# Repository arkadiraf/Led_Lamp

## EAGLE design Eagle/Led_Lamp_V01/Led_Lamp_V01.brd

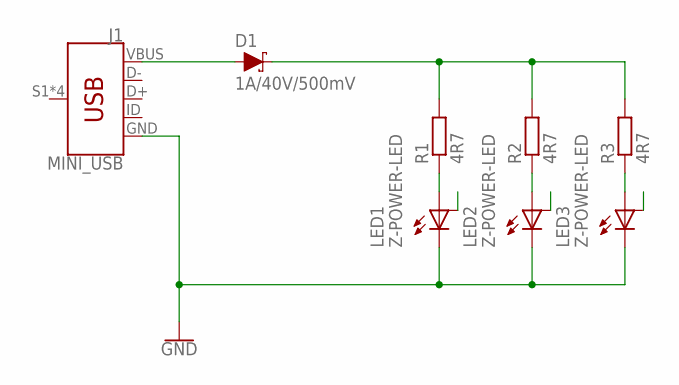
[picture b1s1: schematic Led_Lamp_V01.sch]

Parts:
D1: 1A/40V/500mV; SMA-DIODE
J1: MINI_USB; USB-MINIB
LED1, LED2, LED3: Z-POWER-LED; Z-POWER-LED-PCB-TYPE
R1, R2, R3: 4R7; R2512

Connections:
GND: J1.GND, LED1.C, LED2.C, LED3.C
unnamed: D1.A, J1.VBUS
unnamed: D1.C, R1.2, R2.2, R3.2
unnamed: LED3.A, R3.1
unnamed: LED2.A, R2.1
unnamed: LED1.A, R1.1
PAD: LED1.PAD, LED2.PAD, LED3.PAD

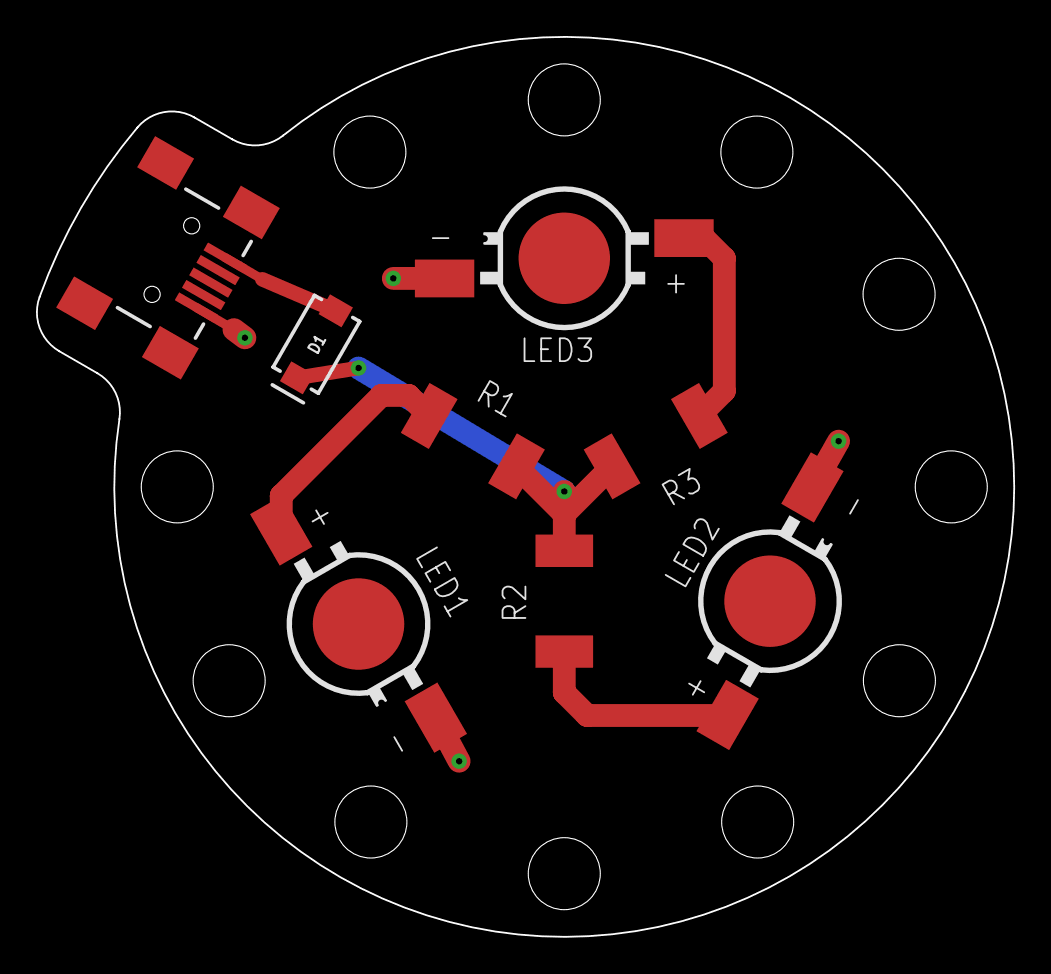
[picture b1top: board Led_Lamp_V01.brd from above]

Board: 2 copper layers, 54.3 x 50.0 mm, 8 parts (0 on the bottom side), 7 nets.

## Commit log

2017-10-10 Update 10_10_17
2017-10-10 Updated Photos
2017-11-02 Photo_Update

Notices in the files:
parts and their libraries:
SparkFun-Connectors: Licensing: Creative Commons ShareAlike 4.0 International - https://creativecommons.org/licenses/by-sa/4.0
